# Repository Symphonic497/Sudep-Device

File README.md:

# Sudep Device
 Eagle Schematic and PCB files for the SUDEP device

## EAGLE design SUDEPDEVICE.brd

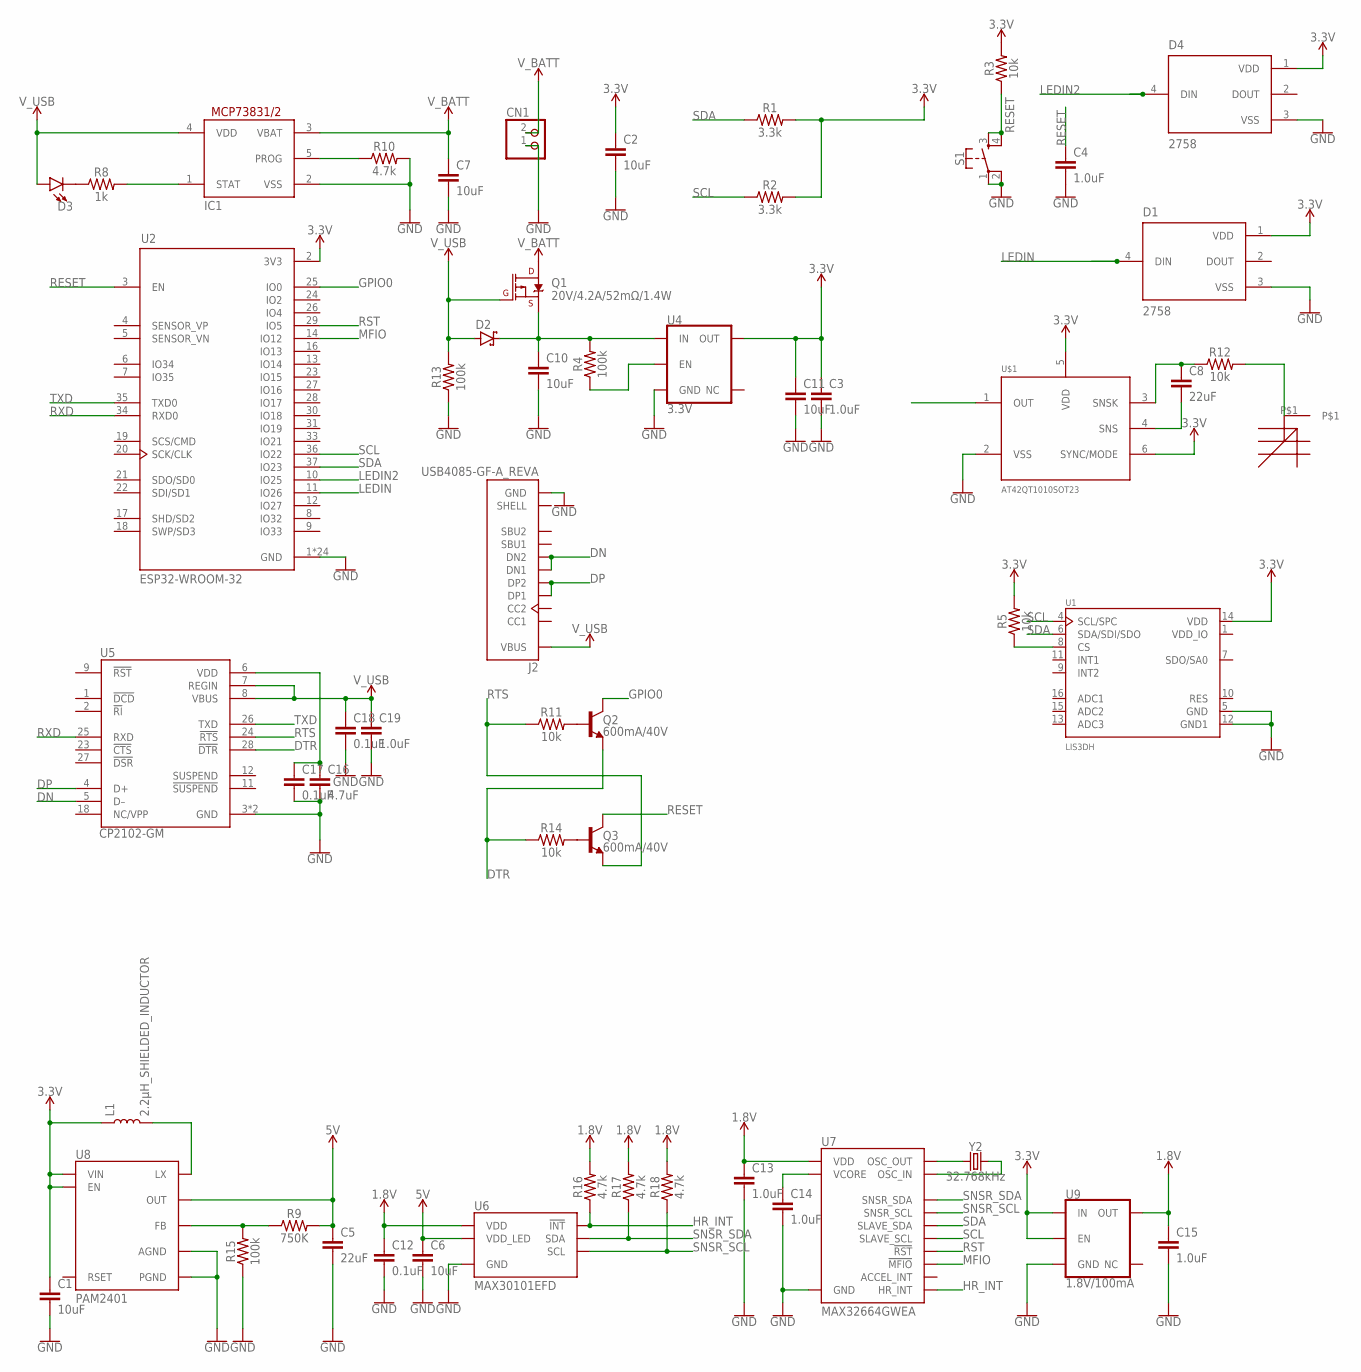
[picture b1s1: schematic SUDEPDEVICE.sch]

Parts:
C1, C2, C6, C7, C10, C11: 10uF; 0603
C3, C4, C13, C14, C15, C19: 1.0uF; 0603
C5, C8: 22uF; 0603
C12, C17, C18: 0.1uF; 0603
C16: 4.7uF; 0603
CN1: JST_2PIN-SMT-RA; JST-PH-2-SMT-RA
D1, D4: 2758; SOL320P540X170-4N
D2: SCHOTTKY-DIODESMD; SMB
D3: LED0603; LED-0603
IC1: MCP73831/OT; SOT23-5L
J2: USB4085-GF-A_REVA; GCT_USB4085-GF-A_REVA
L1: 2.2μH_SHIELDED_INDUCTOR; 0806
Q1: 20V/4.2A/52mΩ/1.4W; SOT23-3
Q2, Q3: 600mA/40V; SOT23-3
R1, R2: 3.3k; 0603
R3, R5, R11, R12, R14: 10k; 0603
R4, R13, R15: 100k; 0603
R8: 1k; 0603
R9: 750K; 0603
R10, R16, R17, R18: 4.7k; 0603
S1: MOMENTARY-SWITCH-SPST-2-SMD-4.6X2.8MM; TACTILE_SWITCH_SMD_4.6X2.8MM
U1: LIS3DH; PQFN50P300X300X100-16N
U2: ESP32-WROOM-32; MODULE_ESP32-WROOM-32
U4: 3.3V; SOT23-5
U5: CP2102-GM; QFN50P500X500X100-29N
U6: MAX30101EFD; 14_PIN_OESIP
U7: MAX32664GWEA; 16_PIN_WLP
U8: PAM2401; MSOP8
U9: 1.8V/100mA; SC70
U$1: AT42QT1010SOT23; SOT23-6
U$2: RMARTIN-CUSTOM-LIBRARY_CAP_SENSOR_5X10
Y2: 32.768kHz; CRYSTAL-SMD-3.2X1.5MM

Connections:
1.8V: C12.1, C13.1, C15.1, R16.2, R17.2, R18.2, U6.P11 (VDD), U7.3 (VDD), U9.5 (OUT)
3.3V: C1.1, C2.1, C3.1, C11.1, D1.1 (VDD), D4.1 (VDD), L1.1, R1.2, R2.2, R3.2, R5.2, U1.14 (VDD), U2.2 (3V3), U4.5 (OUT), U8.2 (EN), U8.3 (VIN), U9.1 (IN), U9.3 (EN), U$1.5 (VDD), U$1.6 (SYNC/MODE)
5V: C5.1, C6.1, R9.2, U6.P9 (VDD_LED), U6.P10 (VDD_LED), U8.7 (OUT)
DN: J2.A7 (DN1), J2.B7 (DN2), U5.5 (D–)
DP: J2.A6 (DP1), J2.B6 (DP2), U5.4 (D+)
DTR: Q2.2 (E), R14.1, U5.28 (!DTR)
GND: C1.2, C2.2, C3.2, C4.2, C5.2, C6.2, C7.2, C10.2, C11.2, C12.2, C13.2, C14.2, C15.2, C16.2, C17.2, C18.2, C19.2, CN1.1 (2), D1.3 (VSS), D4.3 (VSS), IC1.2 (VSS), J2.A1 (GND), J2.A12 (GND), J2.B1 (GND), J2.B12 (GND), R10.2, R13.1, R15.1, S1.1, S1.2, U1.5 (GND), U1.12 (GND1), U2.1 (GND), U2.15 (GND), U2.38 (GND), U2.39_1 (GND), U2.39_2 (GND), U2.39_3 (GND), U2.39_4 (GND), U2.39_5 (GND), U2.39_6 (GND), U2.39_7 (GND), U2.39_8 (GND), U2.39_9 (GND), U2.39_10 (GND), U2.39_11 (GND), U2.39_12 (GND), U2.39_13 (GND), U2.39_14 (GND), U2.39_15 (GND), U2.39_16 (GND), U2.39_17 (GND), U2.39_18 (GND), U2.39_19 (GND), U2.39_20 (GND), U2.39_21 (GND), U4.2 (GND), U5.3 (GND), U5.29 (GND), U6.P4 (GND), U6.P12 (GND), U7.13 (GND), U8.4 (AGND), U8.8 (PGND), U9.2 (GND), U$1.2 (VSS)
GPIO0: Q2.3 (C), U2.25 (IO0)
HR_INT: R16.1, U6.P13 (!INT), U7.6 (HR_INT)
LEDIN: D1.4 (DIN), U2.11 (IO26)
LEDIN2: D4.4 (DIN), U2.10 (IO25)
MFIO: U2.14 (IO12), U7.16 (!MFIO)
unnamed: R4.1, U4.3 (EN)
unnamed: R9.1, R15.2, U8.5 (FB)
unnamed: C10.1, D2.C, Q1.2 (S), R4.2, U4.1 (IN)
unnamed: IC1.5 (PROG), R10.1
unnamed: R5.1, U1.8 (CS)
unnamed: IC1.1 (STAT), R8.2
unnamed: C8.2, U$1.4 (SNS)
unnamed: Q2.1 (B), R11.2
unnamed: Q3.1 (B), R14.2
unnamed: D3.C, R8.1
unnamed: C8.1, R12.1, U$1.3 (SNSK)
unnamed: R12.2, U$2.P$1
unnamed: L1.2, U8.1 (LX)
unnamed: C14.1, U7.4 (VCORE)
unnamed: U7.1 (OSC_OUT), Y2.P$1 (1)
unnamed: U7.2 (OSC_IN), Y2.P$2 (2)
unnamed: C16.1, C17.1, U5.6 (VDD)
RES: U1.10 (RES)
RESET: C4.1, Q3.3 (C), R3.1, S1.3, S1.4, U2.3 (EN)
RST: U2.29 (IO5), U7.12 (!RST)
RTS: Q3.2 (E), R11.1, U5.24 (!RTS)
RXD: U2.34 (RXD0), U5.25 (RXD)
SCL: R2.1, U1.4 (SCL/SPC), U2.36 (IO22), U7.10 (SLAVE_SCL)
SDA: R1.1, U1.6 (SDA/SDI/SDO), U2.37 (IO23), U7.9 (SLAVE_SDA)
SNSR_SCL: R18.1, U6.P2 (SCL), U7.5 (SNSR_SCL)
SNSR_SDA: R17.1, U6.P3 (SDA), U7.14 (SNSR_SDA)
TXD: U2.35 (TXD0), U5.26 (TXD)
VDD_IO: U1.1 (VDD_IO)
V_BATT: C7.1, CN1.2 (1), IC1.3 (VBAT), Q1.3 (D)
V_USB: C18.1, C19.1, D2.A, D3.A, IC1.4 (VDD), J2.A4 (VBUS), J2.A9 (VBUS), J2.B4 (VBUS), J2.B9 (VBUS), Q1.1 (G), R13.2, U5.7 (REGIN), U5.8 (VBUS)

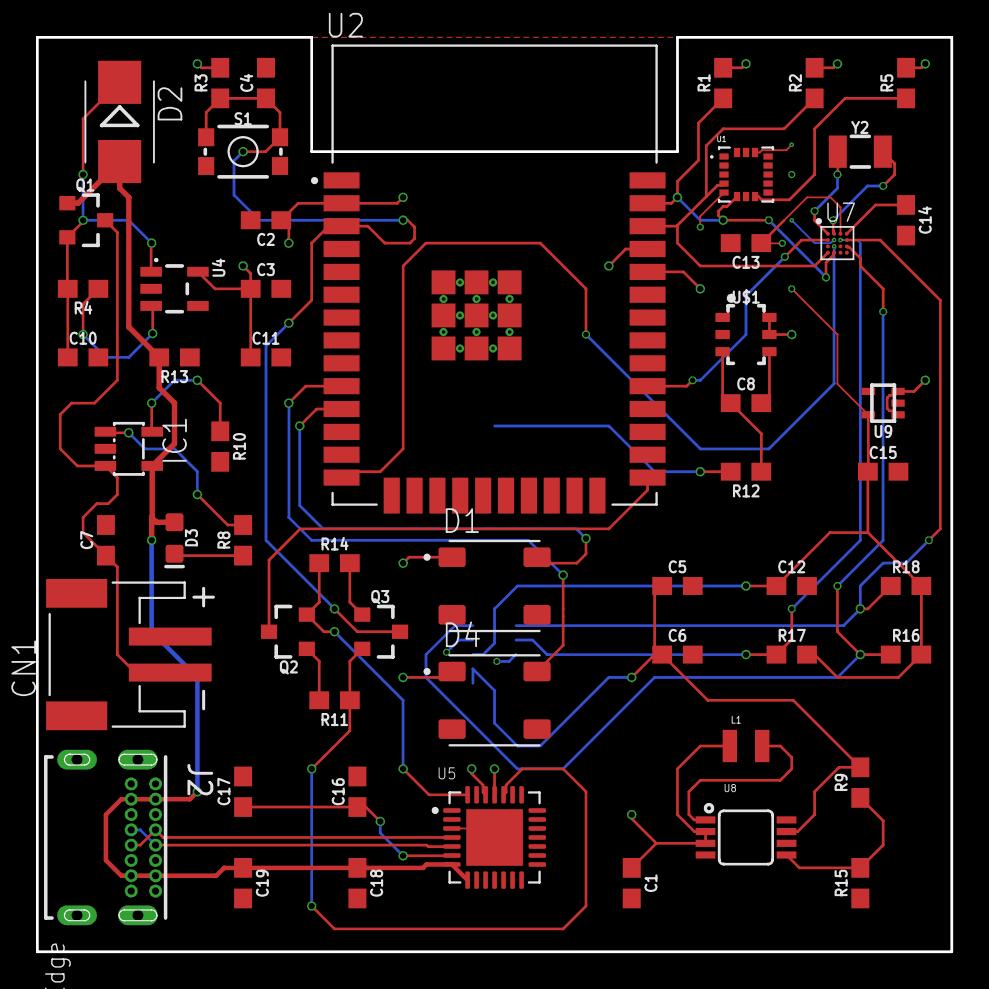
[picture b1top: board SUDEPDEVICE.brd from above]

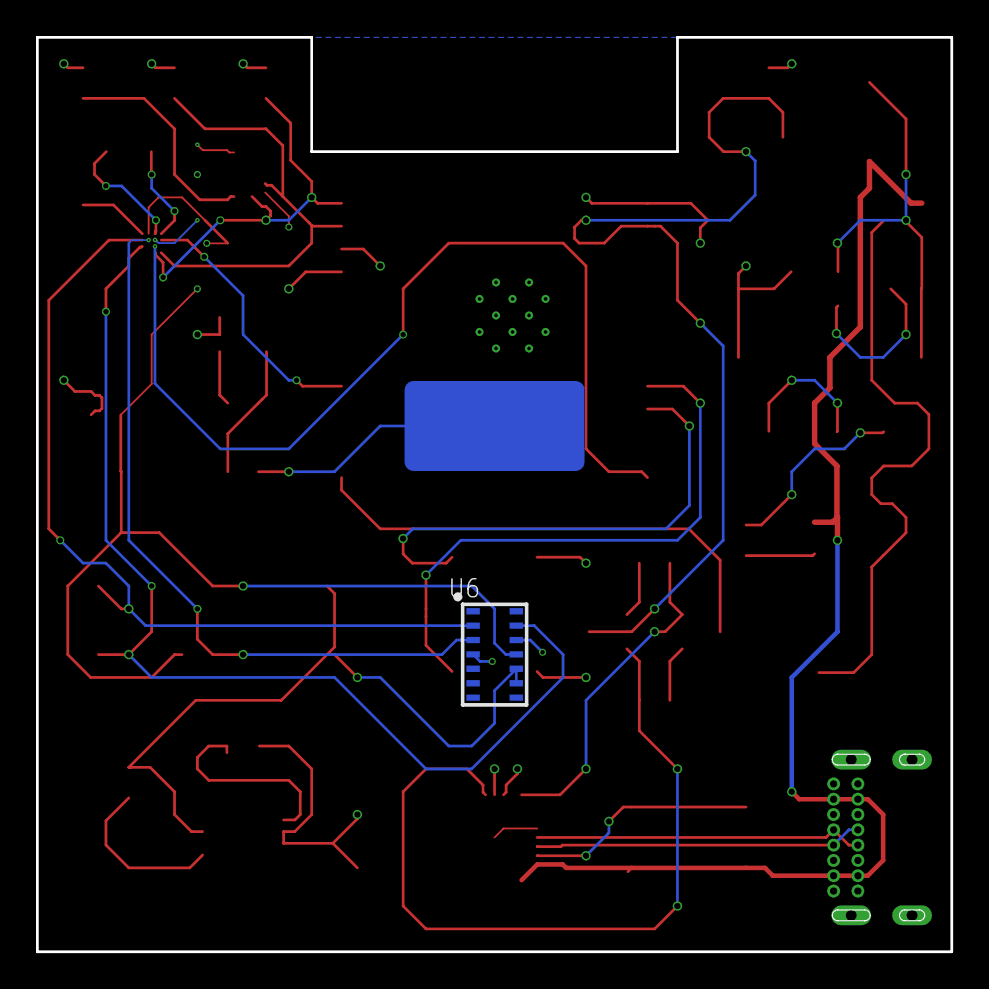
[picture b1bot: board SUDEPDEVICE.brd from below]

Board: 4 copper layers, 50.8 x 50.8 mm, 57 parts (2 on the bottom side), 40 nets.

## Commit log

2022-02-23 Init

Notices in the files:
parts and their libraries:
SparkFun-Capacitors: Licensing: Creative Commons ShareAlike 4.0 International - https://creativecommons.org/licenses/by-sa/4.0
